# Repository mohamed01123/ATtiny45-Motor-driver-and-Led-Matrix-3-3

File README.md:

ATtiny45 Motor Driver and 3x3 LED Matrix

 Overview

This project is a simple **educational circuit** . It combines a **DC motor driver (H-bridge)** and a **3x3 LED matrix** controlled by an **ATtiny45 microcontroller**. It also includes a **buzzer** and is powered through an external **power source with a switch**.

 🔧 **Note:** The software part of the project is not developed by me. This project mainly focuses on the **hardware design**.

 Features

* Control a DC motor using a custom **H-Bridge circuit** (built from 4x NPN transistors: 2N2222 or BC547).
* Display patterns using a 3x3 LED matrix**.
* Output sound via a **buzzer**.
* All components are **controlled by an ATtiny45**.
* Powered through an external supply with a **manual switch**.

 Components Used

* ATtiny45 microcontroller
* 4x NPN Transistors (BC547) for H-Bridge
* DC Motor
* 3x3 LED Matrix
* Buzzer
* Power Source (battery or adapter)
* Switch
* Resistors and wiring

 Circuit Design

The project is centered around the ATtiny45 which is responsible for controlling the motor direction (via H-Bridge), LED matrix display, and buzzer. The motor driver (H-Bridge) is built manually using four NPN transistors.

 Purpose

This project was built for **educational purposes** to demonstrate:

* Motor control using transistors
* LED matrix control via microcontroller
* Basic embedded systems design using ATtiny45

 License

This project is shared for educational purposes only. Feel free to use or modify the hardware design.

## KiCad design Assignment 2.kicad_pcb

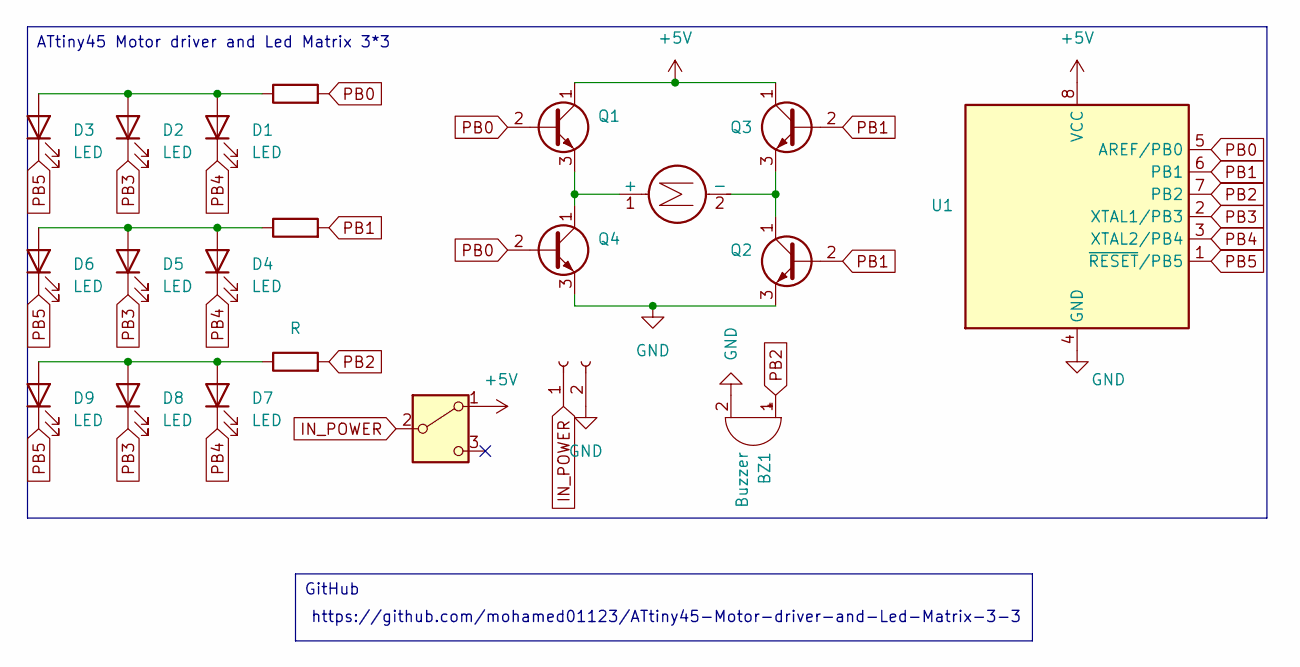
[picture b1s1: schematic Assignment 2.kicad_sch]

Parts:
BZ1: Buzzer; Buzzer_12x9.5RM7.6
D1, D2, D3, D4, D5, D6, D7, D8, D9: LED; LED_D3.0mm
J1: Conn_01x02_Socket; TerminalBlock_Phoenix_PT-1,5-2-3.5-H_1x02_P3.50mm_Horizontal
M1: Motor_DC; PinHeader_1x02_P1.27mm_Vertical
Q1, Q2, Q3, Q4: BC547; TO-92_Inline
R1, R2, R3: R; R_Axial_DIN0204_L3.6mm_D1.6mm_P5.08mm_Horizontal
SW1: SW_DPDT_x2; SW_CK_JS202011CQN_DPDT_Straight
U1: ATtiny45-20P; DIP-8_W7.62mm

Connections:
+5V: Q1.1 (C), Q3.1 (C), SW1.1 (A), U1.8 (VCC)
GND: BZ1.2 (-), J1.2, Q2.3 (E), Q4.3 (E), U1.4 (GND)
IN_POWER: J1.1, SW1.2 (B)
unnamed: D1.2 (A), D2.2 (A), D3.2 (A), R1.1
unnamed: D4.2 (A), D5.2 (A), D6.2 (A), R2.1
unnamed: D7.2 (A), D8.2 (A), D9.2 (A), R3.1
unnamed: M1.1 (+), Q1.3 (E), Q4.1 (C)
unnamed: M1.2 (-), Q2.1 (C), Q3.3 (E)
PB0: Q1.2 (B), Q4.2 (B), R1.2, U1.5 (AREF/PB0)
PB1: Q2.2 (B), Q3.2 (B), R2.2, U1.6 (PB1)
PB2: BZ1.1 (+), R3.2, U1.7 (PB2)
PB3: D2.1 (K), D5.1 (K), D8.1 (K), U1.2 (XTAL1/PB3)
PB4: D1.1 (K), D4.1 (K), D7.1 (K), U1.3 (XTAL2/PB4)
PB5: D3.1 (K), D6.1 (K), D9.1 (K), U1.1 (~RESET/PB5)

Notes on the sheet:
https://github.com/mohamed01123/ATtiny45-Motor-driver-and-Led-Matrix-3-3
ATtiny45 Motor driver and Led Matrix 3*3
GitHub

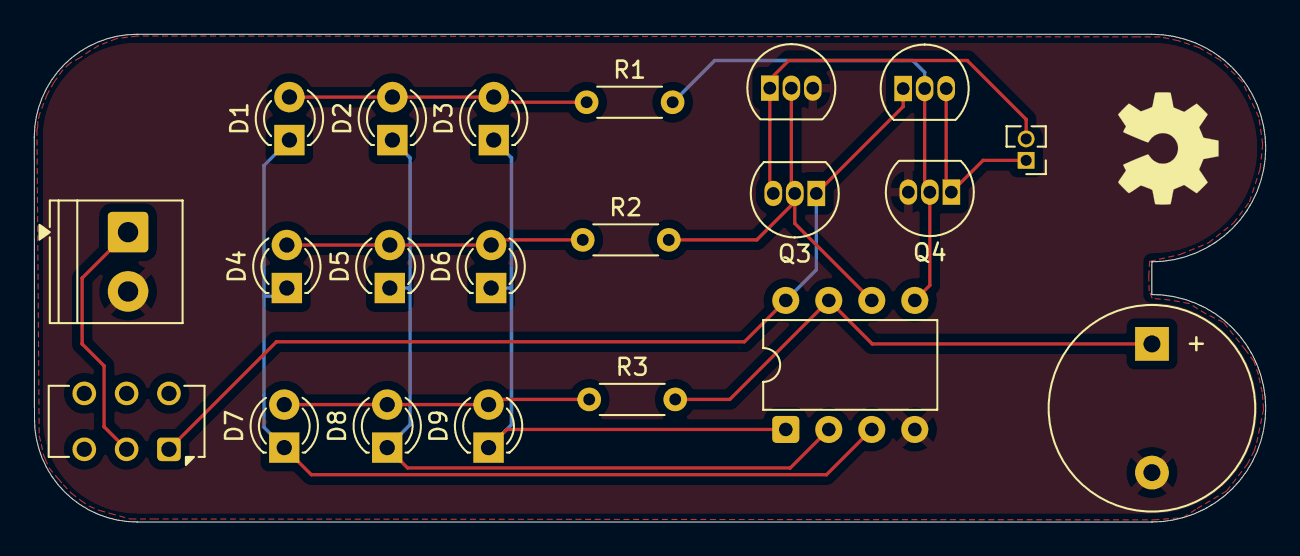
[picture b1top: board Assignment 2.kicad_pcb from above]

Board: 2 copper layers, 72.7 x 28.8 mm, 21 parts (0 on the bottom side), 14 nets.

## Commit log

2025-05-24 The frist commit
